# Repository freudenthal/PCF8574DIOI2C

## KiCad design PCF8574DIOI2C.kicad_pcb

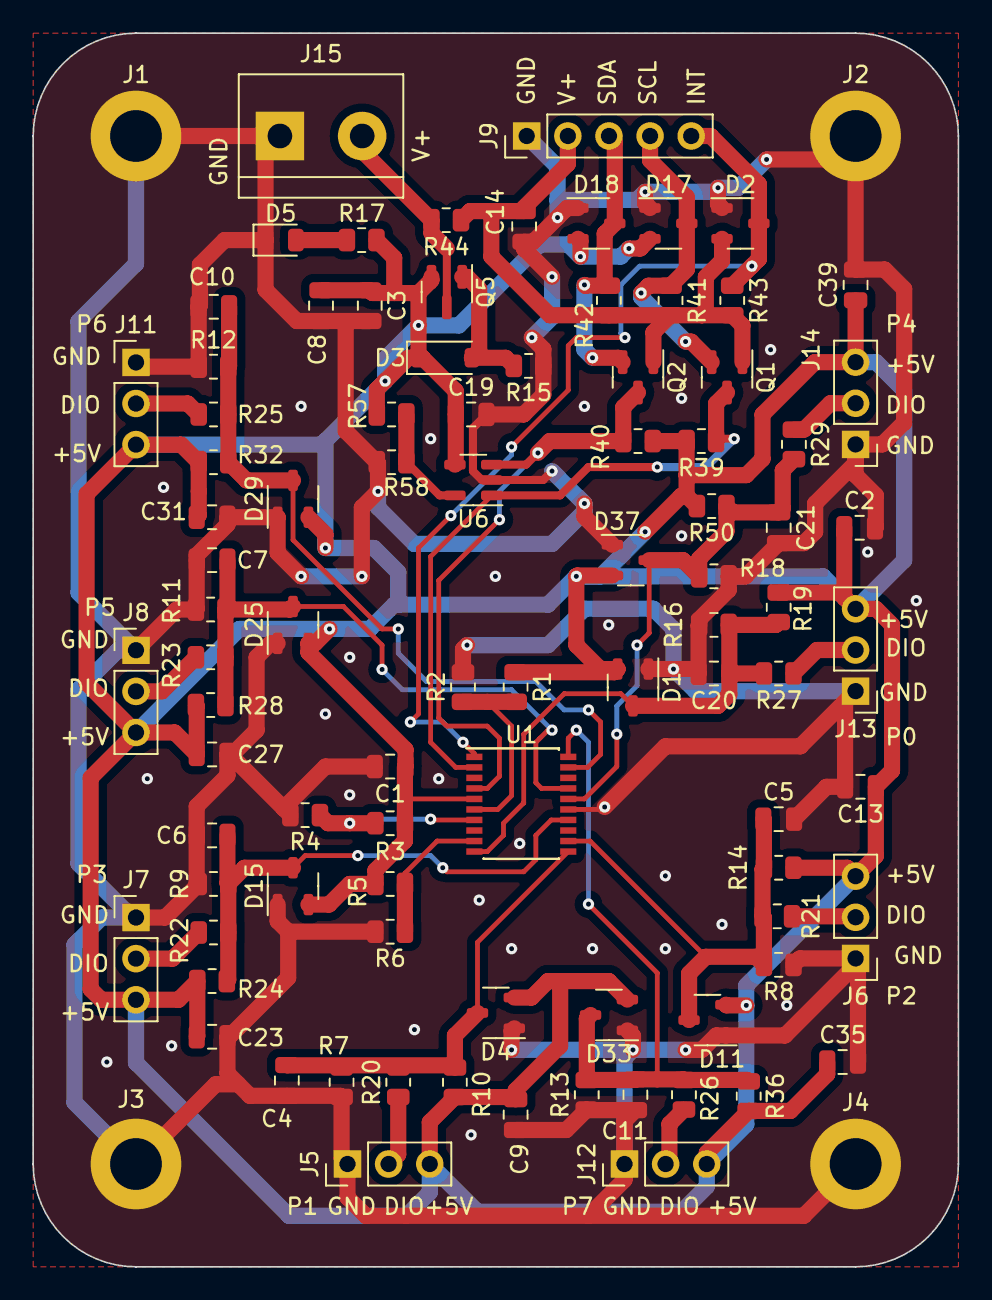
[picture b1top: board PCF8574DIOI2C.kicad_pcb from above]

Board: 2 copper layers, 57.1 x 76.2 mm, 93 parts (0 on the bottom side), 31 nets.

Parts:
C1, C2, C4, C5, C6, C7, C8, C9, C10, C11, C13, C14, C19, C20, C21, C23, C27, C31, C35, C39: 1uF; C_0805_2012Metric
C3: 10uF; C_0805_2012Metric
D1, D2, D4, D11, D15, D17, D18, D25, D29, D33, D37: 100V; SOT-23-3
D3: 10V; D_SOD-123
D5: LED; LED_0805_2012Metric
J1, J2, J3, J4: M3; MountingHole_3.2mm_M3_DIN965_Pad
J5, J6, J7, J8, J11, J12, J13, J14: DIO; PinHeader_1x03_P2.54mm_Vertical
J9: I2C; PinHeader_1x05_P2.54mm_Vertical
J15: Vin; TerminalBlock_bornier-2_P5.08mm
Q1, Q2: Q_NMOS_GSD; SOT-23
Q5: Q_PMOS_GSD; SOT-23
R1, R2, R3, R4, R5, R6, R39, R40, R41, R42, R43, R57, R58: 10kΩ; R_0805_2012Metric
R7, R8, R9, R10, R11, R12, R13, R14, R16, R18, R19, R20, R21, R22, R23, R24, R25, R26, R27, R28, R29, R32, R36, R50: 1.2kΩ; R_0805_2012Metric
R15: 100kΩ; R_0805_2012Metric
R17: 500Ω; R_0805_2012Metric
R44: NS; R_0805_2012Metric
U1: PCF8574TS; SSOP-20_4.4x6.5mm_P0.65mm
U6: 24FC01T-I/OT; SOT-23-5

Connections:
+5V: C1.1, C2.1, C3.1, C8.1, C9.1, C13.1, C19.1, C23.1, C27.1, C31.1, C35.1, C39.1, D1.2 (K), D3.1 (K), D4.2 (K), D11.2 (K), D15.2 (K), D17.2 (K), D18.2 (K), D25.2 (K), D29.2 (K), D33.2 (K), D37.2 (K), J5.3, J6.3, J7.3, J8.3, J11.3, J12.3, J13.3, J14.3, Q5.2 (S), R1.1, R3.1, R5.1, R10.2, R14.2, R17.2, R19.2, R24.2, R28.2, R32.2, R36.2, R39.2, R40.2, R50.2, R57.2, U1.5 (VDD), U6.4 (V_{CC})
/EEPROMI2C/SCL: Q1.3 (D), R39.1, U1.2 (SCL), U6.1 (SCL)
/EEPROMI2C/SDA: Q2.3 (D), R40.1, U1.4 (SDA), U6.3 (SDA)
/I2CConnector/INT: D2.3 (A), J9.5, R43.1, U1.1 (~INT)
/I2CConnector/VI2C: C14.1, D2.2 (K), J9.2, Q1.1 (G), Q2.1 (G), R41.2, R42.2, R43.2, R44.1
/PCF8574/A0: R1.2, R2.1, U1.6 (A0)
/PCF8574/A1: R3.2, R4.1, U1.7 (A1)
/PCF8574/A2: R5.2, R6.1, U1.9 (A2)
/PCF8574/HighSideGate1/IN: C4.1, D4.3 (A), R7.2, R10.1, R20.2, U1.11 (P1)
/PCF8574/HighSideGate2/IN: C5.1, D11.3 (A), R8.2, R14.1, R21.2, U1.12 (P2)
/PCF8574/HighSideGate3/IN: C6.1, D15.3 (A), R9.2, R22.2, R24.1, U1.14 (P3)
/PCF8574/HighSideGate4/IN: C21.1, D37.3 (A), R18.2, R29.2, R50.1, U1.16 (P4)
/PCF8574/HighSideGate5/IN: C7.1, D25.3 (A), R11.2, R23.2, R28.1, U1.17 (P5)
/PCF8574/HighSideGate6/IN: C10.1, D29.3 (A), R12.2, R25.2, R32.1, U1.19 (P6)
/PCF8574/HighSideGate7/IN: C11.1, D33.3 (A), R13.2, R26.2, R36.1, U1.20 (P7)
/PCF8574/HighSideGate/IN: C20.1, D1.3 (A), R16.2, R19.1, R27.2, U1.10 (P0)
GND: C1.2, C2.2, C3.2, C4.2, C5.2, C6.2, C7.2, C8.2, C9.2, C10.2, C11.2, C13.2, C14.2, C19.2, C20.2, C21.2, C23.2, C27.2, C31.2, C35.2, C39.2, D1.1 (K), D2.1 (K), D4.1 (K), D5.1 (K), D11.1 (K), D15.1 (K), D17.1 (K), D18.1 (K), D25.1 (K), D29.1 (K), D33.1 (K), D37.1 (K), J1.1, J2.1, J3.1, J4.1, J5.1, J6.1, J7.1, J8.1, J9.1, J11.1, J12.1, J13.1, J14.1, J15.1, R2.2, R4.2, R6.2, R7.1, R8.1, R9.1, R11.1, R12.1, R13.1, R15.1, R16.1, R18.1, R58.1, U1.15 (VSS), U6.2 (GND)
unnamed: D3.2 (A), Q5.1 (G), R15.2
unnamed: D5.2 (A), R17.1
unnamed: D17.3 (A), J9.4, Q1.2 (S), R41.1
unnamed: D18.3 (A), J9.3, Q2.2 (S), R42.1
unnamed: J5.2, R20.1
unnamed: J6.2, R21.1
unnamed: J7.2, R22.1
unnamed: J8.2, R23.1
unnamed: J11.2, R25.1
unnamed: J12.2, R26.1
unnamed: J13.2, R27.1
unnamed: J14.2, R29.1
unnamed: J15.2, Q5.3 (D), R44.2
unnamed: R57.1, R58.2, U6.5 (WP)
